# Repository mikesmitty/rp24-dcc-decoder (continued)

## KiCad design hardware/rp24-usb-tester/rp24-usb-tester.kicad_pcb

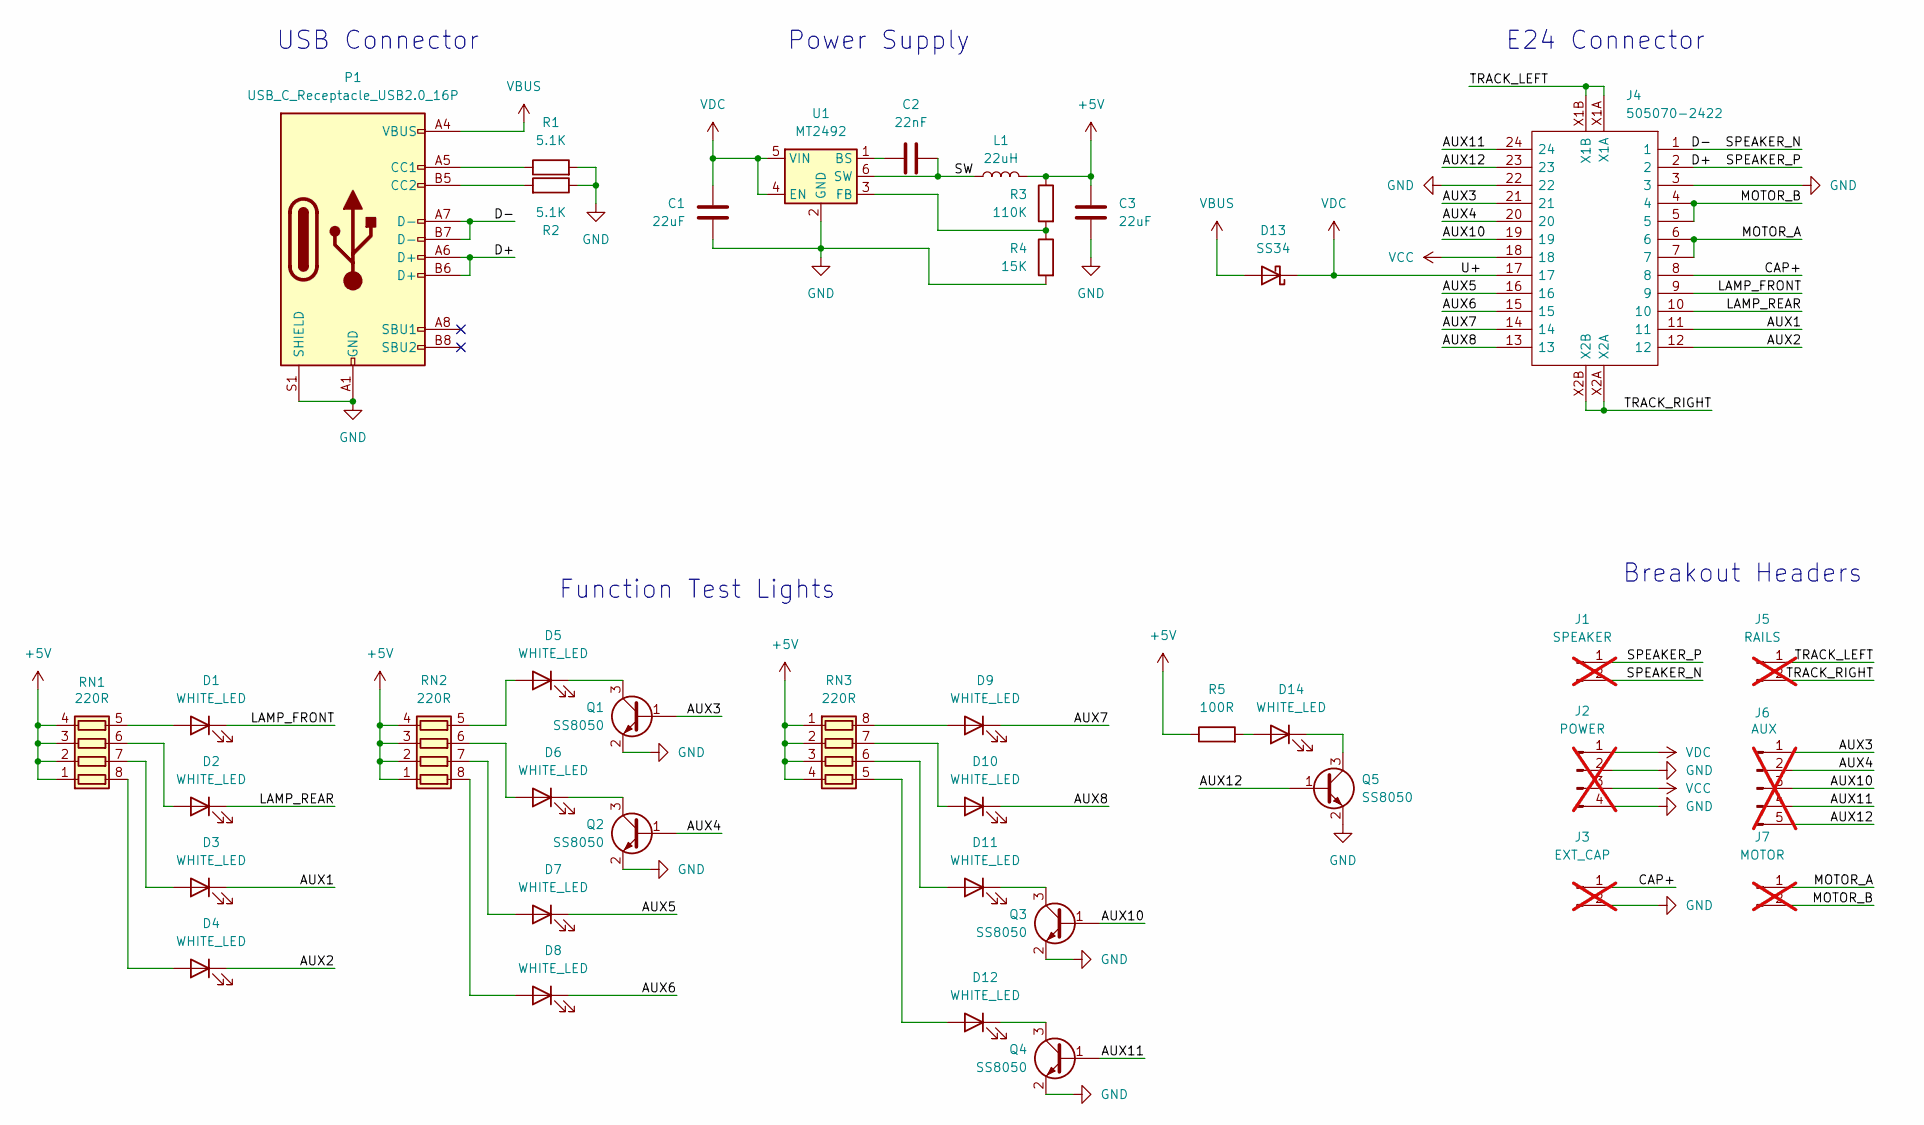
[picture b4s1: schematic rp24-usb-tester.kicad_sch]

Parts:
C1, C3: 22uF; C_0805_2012Metric; LCSC C45783
C2: 22nF; C_0402_1005Metric; LCSC C1532
D1, D2, D3, D4, D5, D6, D7, D8, D9, D10, D11, D12, D14: WHITE_LED; LED_0603_1608Metric; LCSC C2290
D13: SS34; D_SMA; LCSC C8678
J1: SPEAKER; PinHeader_1x02_P2.54mm_Vertical; not fitted
J2: POWER; PinHeader_1x04_P2.54mm_Vertical; not fitted
J3: EXT_CAP; PinHeader_1x02_P2.54mm_Vertical; not fitted
J4: 505070-2422; CONN-SMD_24P-P0.35_5050702422; Manufacturer_Part_Number 505070-2422; LCSC C724143
J5: RAILS; PinHeader_1x02_P2.54mm_Vertical; not fitted
J6: AUX; PinHeader_1x05_P2.54mm_Vertical; not fitted
J7: MOTOR; PinHeader_1x02_P2.54mm_Vertical; not fitted
L1: 22uH; IND-SMD_L4.6-W4.2_SMMS0420; LCSC C2894720
P1: USB_C_Receptacle_USB2.0_16P; USB_C_Receptacle_GCT_USB4105-xx-A_16P_TopMnt_Horizontal; LCSC C2765186
Q1, Q2, Q3, Q4, Q5: SS8050; SOT-23; LCSC C2150
R1, R2: 5.1K; R_0402_1005Metric; LCSC C25905
R3: 110K; R_0603_1608Metric; LCSC C25805
R4: 15K; R_0603_1608Metric; LCSC C22809
R5: 100R; R_0402_1005Metric; LCSC C25076
RN1, RN2, RN3: 220R; R_Array_Concave_4x0402; LCSC C326868
U1: MT2492; SOT-23-6; LCSC C89358

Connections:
+5V: C3.1, L1.2, R3.1, R5.1, RN1.1 (R1.1), RN1.2 (R2.1), RN1.3 (R3.1), RN1.4 (R4.1), RN2.1 (R1.1), RN2.2 (R2.1), RN2.3 (R3.1), RN2.4 (R4.1), RN3.1 (R1.1), RN3.2 (R2.1), RN3.3 (R3.1), RN3.4 (R4.1)
/AUX1: D3.1 (K), J4.11
/AUX2: D4.1 (K), J4.12
/AUX3: J4.21, J6.1, Q1.1 (B)
/AUX4: J4.20, J6.2, Q2.1 (B)
/AUX5: D7.1 (K), J4.16
/AUX6: D8.1 (K), J4.15
/AUX7: D9.1 (K), J4.14
/AUX8: D10.1 (K), J4.13
/AUX10: J4.19, J6.3, Q3.1 (B)
/AUX11: J4.24, J6.4, Q4.1 (B)
/AUX12: J4.23, J6.5, Q5.1 (B)
/CAP+: J3.1, J4.8
/D+: J1.1, J4.2, P1.A6 (D+), P1.B6 (D+)
/D-: J1.2, J4.1, P1.A7 (D-), P1.B7 (D-)
/LAMP_FRONT: D1.1 (K), J4.9
/LAMP_REAR: D2.1 (K), J4.10
/MOTOR_A: J4.6, J4.7, J7.1
/MOTOR_B: J4.4, J4.5, J7.2
/SW: C2.2, L1.1, U1.6 (SW)
/TRACK_LEFT: J4.X1A, J4.X1B, J5.1
/TRACK_RIGHT: J4.X2A, J4.X2B, J5.2
GND: C1.2, C3.2, J2.2, J2.4, J3.2, J4.3, J4.22, P1.A1 (GND), P1.A12 (GND), P1.B1 (GND), P1.B12 (GND), P1.S1 (SHIELD), Q1.2 (E), Q2.2 (E), Q3.2 (E), Q4.2 (E), Q5.2 (E), R1.2, R2.1, R4.2, U1.2 (GND)
unnamed: D1.2 (A), RN1.5 (R4.2)
unnamed: D2.2 (A), RN1.6 (R3.2)
unnamed: D3.2 (A), RN1.7 (R2.2)
unnamed: D4.2 (A), RN1.8 (R1.2)
unnamed: D5.2 (A), RN2.5 (R4.2)
unnamed: D5.1 (K), Q1.3 (C)
unnamed: D6.2 (A), RN2.6 (R3.2)
unnamed: D6.1 (K), Q2.3 (C)
unnamed: D7.2 (A), RN2.7 (R2.2)
unnamed: D8.2 (A), RN2.8 (R1.2)
unnamed: D9.2 (A), RN3.8 (R1.2)
unnamed: D10.2 (A), RN3.7 (R2.2)
unnamed: D11.2 (A), RN3.6 (R3.2)
unnamed: D11.1 (K), Q3.3 (C)
unnamed: D12.2 (A), RN3.5 (R4.2)
unnamed: D12.1 (K), Q4.3 (C)
unnamed: D14.2 (A), R5.2
unnamed: D14.1 (K), Q5.3 (C)
unnamed: P1.A5 (CC1), R1.1
unnamed: P1.B5 (CC2), R2.2
unnamed: C2.1, U1.1 (BS)
unnamed: R3.2, R4.1, U1.3 (FB)
VBUS: D13.2 (A), P1.A4 (VBUS), P1.A9 (VBUS), P1.B4 (VBUS), P1.B9 (VBUS)
VCC: J2.3, J4.18
VDC: C1.1, D13.1 (K), J2.1, J4.17, U1.4 (EN), U1.5 (VIN)

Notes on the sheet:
Function Test Lights
Breakout Headers
E24 Connector
Power Supply
USB Connector

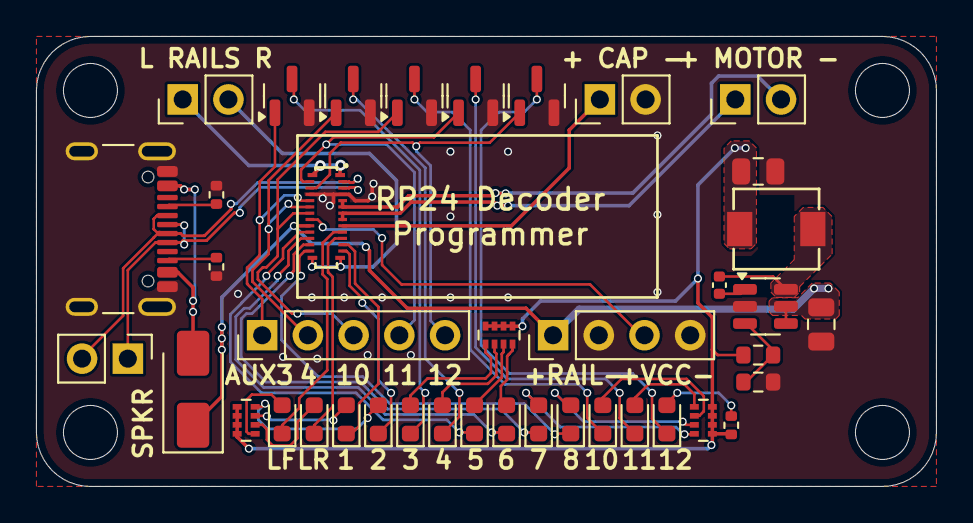
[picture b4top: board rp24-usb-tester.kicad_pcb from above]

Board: 2 copper layers, 50.0 x 25.0 mm, 40 parts (0 on the bottom side), 48 nets.

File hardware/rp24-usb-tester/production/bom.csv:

Comment,Designator,Footprint,LCSC
22uF,"C1,C3",rp24-usb-tester:C_0805_2012Metric,C45783
SS34,D13,rp24-usb-tester:D_SMA,C8678
15K,R4,rp24-usb-tester:R_0603_1608Metric,C22809
WHITE_LED,"D1,D2,D3,D4,D5,D6,D7,D8,D9,D10,D11,D12,D14",rp24-usb-tester:LED_0603_1608Metric,C2290
505070-2422,J4,rp24-usb-tester:CONN-SMD_24P-P0.35_5050702422,C724143
5.1K,"R1,R2",rp24-usb-tester:R_0402_1005Metric,C25905
USB_C_Receptacle_USB2.0_16P,P1,rp24-usb-tester:USB_C_Receptacle_GCT_USB4105-xx-A_16P_TopMnt_Horizontal,C2765186
SS8050,"Q1,Q2,Q3,Q4,Q5",rp24-usb-tester:SOT-23,C2150
220R,"RN1,RN2,RN3",rp24-usb-tester:R_Array_Concave_4x0402,C326868
100R,R5,rp24-usb-tester:R_0402_1005Metric,C25076
22nF,C2,rp24-usb-tester:C_0402_1005Metric,C1532
MT2492,U1,rp24-usb-tester:SOT-23-6,C89358
22uH,L1,rp24-usb-tester:IND-SMD_L4.6-W4.2_SMMS0420,C2894720
110K,R3,rp24-usb-tester:R_0603_1608Metric,C25805

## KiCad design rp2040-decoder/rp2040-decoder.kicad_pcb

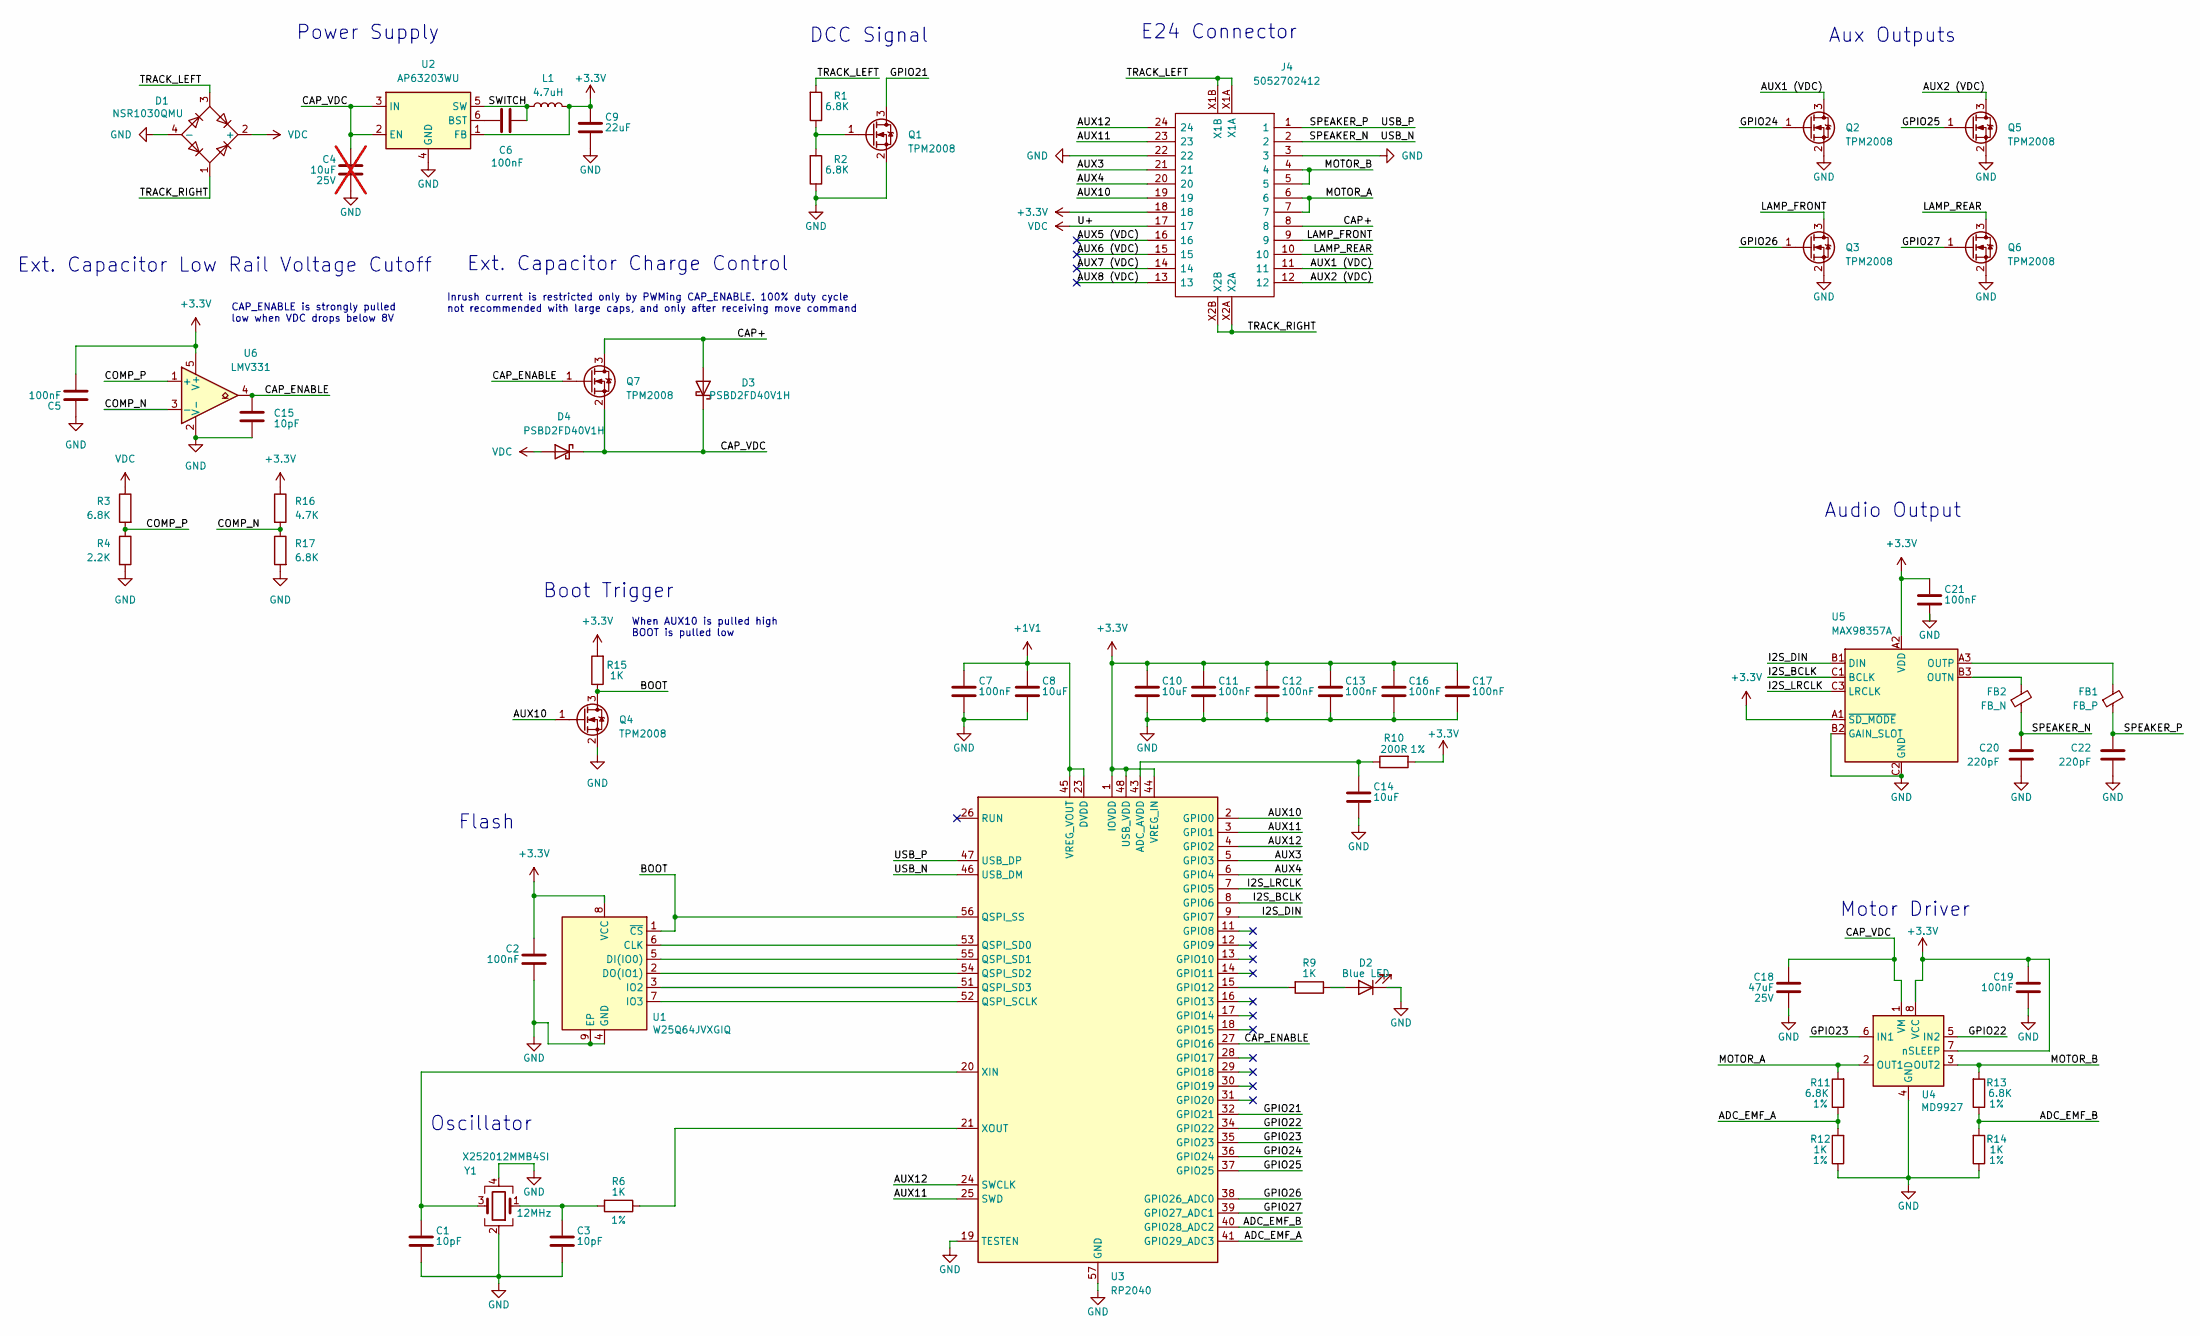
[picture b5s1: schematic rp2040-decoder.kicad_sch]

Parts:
C1, C3, C15: 10pF; C_0201_0603Metric; Voltage 25V; LCSC C384956
C2, C11, C12, C13, C16, C17, C21: 100nF; C_0201_0603Metric; Voltage 6V3; LCSC C49062
C4: 10uF; C_0603_1608Metric; Voltage 25V; LCSC C96446; not fitted
C5, C6, C19: 100nF; C_0201_0603Metric; LCSC C49062
C7: 100nF; C_0201_0603Metric; Voltage 2V5; LCSC C49062
C8: 10uF; C_0402_1005Metric; Voltage 2V5; LCSC C15525
C9: 22uF; C_0603_1608Metric; LCSC C86295
C10, C14: 10uF; C_0402_1005Metric; Voltage 6V3; LCSC C15525
C18: 47uF; C_1206_3216Metric; Voltage 25V; LCSC C403725
C20, C22: 220pF; C_0201_0603Metric; LCSC C62548
D1: NSR1030QMU; LCSC C889734
D2: Blue LED; LED_0402_1005Metric; LCSC C130724
D3, D4: PSBD2FD40V1H; D_SOD-882; LCSC C492733
FB1: FB_P; L_0402_1005Metric; LCSC C160973
FB2: FB_N; L_0402_1005Metric; LCSC C160973
J4: 5052702412; 5050662422; Manufacturer_Part_Number 505270-2412; LCSC C724151
L1: 4.7uH; L_1008_2520Metric; LCSC C5832360
Q1, Q2, Q3, Q4, Q5, Q6, Q7: TPM2008; Diodes_DFN1006-3; LCSC C2827633
R1, R2: 6.8K; R_0201_0603Metric; Tolerance 10%; LCSC C423451
R3, R17: 6.8K; R_0201_0603Metric; LCSC C423451
R4: 2.2K; R_0201_0603Metric; LCSC C473534
R6, R12, R14: 1K; R_0201_0603Metric; Tolerance 1%; LCSC C270365
R9, R15: 1K; R_0201_0603Metric; Tolerance 10%; LCSC C270365
R10: 200R; R_0201_0603Metric; Tolerance 1%; LCSC C270359
R11, R13: 6.8K; R_0201_0603Metric; Tolerance 1%; LCSC C423451
R16: 4.7K; R_0201_0603Metric; LCSC C270346
U1: W25Q64JVXGIQ; WSON-8-1EP_4x4mm_P0.8mm_EP2.2x3mm; LCSC C2940195
U2: AP63203WU; TSOT-23-6; LCSC C780769
U3: RP2040; QFN-56-1EP_7x7mm_P0.4mm_EP3.2x3.2mm; LCSC C2040
U4: MD9927; LM293QT; LCSC C2684662
U5: MAX98357A; Maxim_WLP-9_1.595x1.415_Layout3x3_P0.4mm_Ball0.27mm_Pad0.25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; LCSC C2682619
U6: LMV331; SOT-353_SC-70-5; LCSC C7976
Y1: X252012MMB4SI; Crystal_SMD_2520-4Pin_2.5x2.0mm; LCSC C2896601

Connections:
+1V1: C7.1, C8.1, U3.23 (DVDD), U3.45 (VREG_VOUT), U3.50 (DVDD)
+3.3V: C2.1, C5.2, C9.1, C10.1, C11.1, C12.1, C13.1, C16.1, C17.1, C19.1, C21.1, J4.18, L1.2, R10.1, R15.2, R16.1, U1.8 (VCC), U2.1 (FB), U3.1 (IOVDD), U3.10 (IOVDD), U3.22 (IOVDD), U3.33 (IOVDD), U3.42 (IOVDD), U3.44 (VREG_IN), U3.48 (USB_VDD), U3.49 (IOVDD), U4.7 (nSLEEP), U4.8 (VCC), U5.A1 (~SD_MODE), U5.A2 (VDD), U6.5 (V+)
/ADC_EMF_A: R11.1, R12.2, U3.41 (GPIO29_ADC3)
/ADC_EMF_B: R13.1, R14.2, U3.40 (GPIO28_ADC2)
/AUX1 (VDC): J4.11, Q2.3 (D)
/AUX2 (VDC): J4.12, Q5.3 (D)
/AUX3: J4.21, U3.5 (GPIO3)
/AUX4: J4.20, U3.6 (GPIO4)
/AUX5 (VDC): J4.16
/AUX6 (VDC): J4.15
/AUX7 (VDC): J4.14
/AUX8 (VDC): J4.13
/AUX10: J4.19, Q4.1 (G), U3.2 (GPIO0)
/AUX11: J4.23, U3.3 (GPIO1), U3.25 (SWD)
/AUX12: J4.24, U3.4 (GPIO2), U3.24 (SWCLK)
/BOOT: Q4.3 (D), R15.1, U1.1 (~CS), U3.56 (QSPI_SS)
/CAP+: D3.2 (A), J4.8, Q7.3 (D)
/CAP_ENABLE: C15.1, Q7.1 (G), U3.27 (GPIO16), U6.4
/CAP_VDC: C4.1, C18.1, D3.1 (K), D4.1 (K), Q7.2 (S), U2.2 (EN), U2.3 (IN), U4.1 (VM)
/COMP_N: R16.2, R17.1, U6.3 (-)
/COMP_P: R3.2, R4.1, U6.1 (+)
/GPIO21: Q1.3 (D), U3.32 (GPIO21)
/GPIO22: U3.34 (GPIO22), U4.5 (IN2)
/GPIO23: U3.35 (GPIO23), U4.6 (IN1)
/GPIO24: Q2.1 (G), U3.36 (GPIO24)
/GPIO25: Q5.1 (G), U3.37 (GPIO25)
/GPIO26: Q3.1 (G), U3.38 (GPIO26_ADC0)
/GPIO27: Q6.1 (G), U3.39 (GPIO27_ADC1)
/I2S_BCLK: U3.8 (GPIO6), U5.C1 (BCLK)
/I2S_DIN: U3.9 (GPIO7), U5.B1 (DIN)
/I2S_LRCLK: U3.7 (GPIO5), U5.C3 (LRCLK)
/LAMP_FRONT: J4.9, Q3.3 (D)
/LAMP_REAR: J4.10, Q6.3 (D)
/MOTOR_A: J4.6, J4.7, R11.2, U4.2 (OUT1)
/MOTOR_B: J4.4, J4.5, R13.2, U4.3 (OUT2)
/SPEAKER_N: C20.1, FB2.1, J4.2, U3.46 (USB_DM)
/SPEAKER_P: C22.1, FB1.1, J4.1, U3.47 (USB_DP)
/SWITCH: C6.2, L1.1, U2.5 (SW)
/TRACK_LEFT: D1.3, J4.X1A, J4.X1B, R1.2
/TRACK_RIGHT: D1.1, J4.X2A, J4.X2B
GND: C1.2, C2.2, C3.2, C4.2, C5.1, C7.2, C8.2, C9.2, C10.2, C11.2, C12.2, C13.2, C14.2, C15.2, C16.2, C17.2, C18.2, C19.2, C20.2, C21.2, C22.2, D1.4 (-), D2.1 (K), J4.3, J4.22, Q1.2 (S), Q2.2 (S), Q3.2 (S), Q4.2 (S), Q5.2 (S), Q6.2 (S), R2.1, R4.2, R12.1, R14.1, R17.2, U1.4 (GND), U1.9 (EP), U2.4 (GND), U3.19 (TESTEN), U3.57 (GND), U4.4 (GND), U4.9 (GND), U5.B2 (GAIN_SLOT), U5.C2 (GND), U6.2 (V-), Y1.2, Y1.4
unnamed: C3.1, R6.2, Y1.1
unnamed: D2.2 (A), R9.1
unnamed: Q1.1 (G), R1.1, R2.2
unnamed: U1.6 (CLK), U3.53 (QSPI_SD0)
unnamed: U1.5 (DI(IO0)), U3.55 (QSPI_SD1)
unnamed: U1.2 (DO(IO1)), U3.54 (QSPI_SD2)
unnamed: U1.3 (IO2), U3.51 (QSPI_SD3)
unnamed: U1.7 (IO3), U3.52 (QSPI_SCLK)
unnamed: C6.1, U2.6 (BST)
unnamed: C14.1, R10.2, U3.43 (ADC_AVDD)
unnamed: R9.2, U3.15 (GPIO12)
unnamed: C1.1, U3.20 (XIN), Y1.3
unnamed: R6.1, U3.21 (XOUT)
unnamed: FB2.2, U5.B3 (OUTN)
unnamed: FB1.2, U5.A3 (OUTP)
VDC: D1.2 (+), D4.2 (A), J4.17, R3.1

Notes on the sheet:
Inrush current is restricted only by PWMing CAP_ENABLE. 100% duty cycle not recommended with large caps, and only after receiving move command
Boot Trigger
CAP_ENABLE is strongly pulled low when VDC drops below 8V
Aux Outputs
Motor Driver
Oscillator
Power Supply
Flash
Ext. Capacitor Low Rail Voltage Cutoff
Ext. Capacitor Charge Control
Audio Output
E24 Connector
When AUX10 is pulled high BOOT is pulled low
DCC Signal

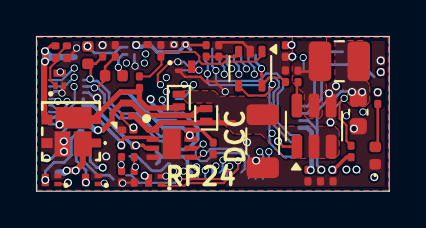
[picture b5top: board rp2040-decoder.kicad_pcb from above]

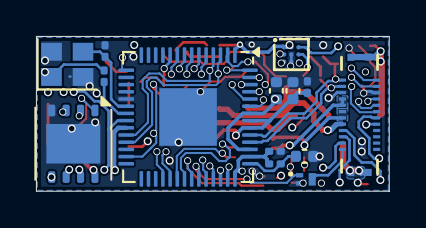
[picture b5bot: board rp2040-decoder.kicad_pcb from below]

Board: 4 copper layers, 19.6 x 8.6 mm, 57 parts (14 on the bottom side), 53 nets.

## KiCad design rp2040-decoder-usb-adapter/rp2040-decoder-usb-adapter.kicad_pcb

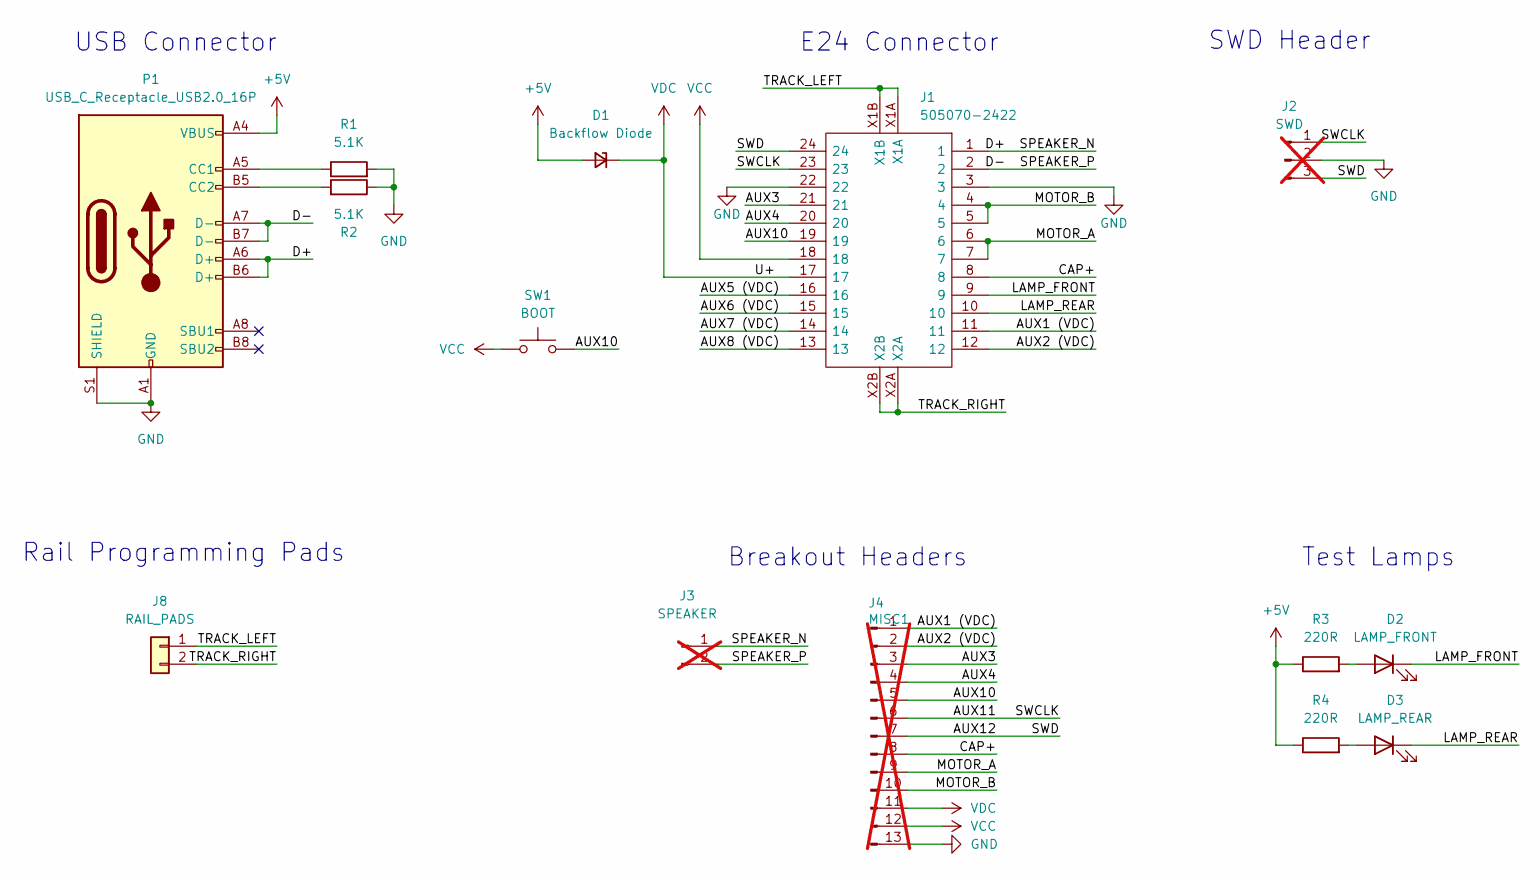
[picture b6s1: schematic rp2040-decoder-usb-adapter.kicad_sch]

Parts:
D1: Backflow Diode; D_SOD-323_HandSoldering; LCSC C2903905
D2: LAMP_FRONT; LED_0603_1608Metric_Pad1.05x0.95mm_HandSolder; LCSC C2290
D3: LAMP_REAR; LED_0603_1608Metric_Pad1.05x0.95mm_HandSolder; LCSC C2290
J1: 505070-2422; 5050702422; Manufacturer_Part_Number 505070-2422; LCSC C724143
J2: SWD; PinHeader_1x03_P2.54mm_Vertical; not fitted
J3: SPEAKER; PinHeader_1x02_P2.54mm_Vertical; not fitted
J4: MISC1; PinHeader_1x13_P2.54mm_Vertical; not fitted
J8: RAIL_PADS; N_Gauge_Rail
P1: USB_C_Receptacle_USB2.0_16P; USB_C_Receptacle_GCT_USB4105-xx-A_16P_TopMnt_Horizontal; LCSC C2765186
R1, R2: 5.1K; R_0805_2012Metric_Pad1.20x1.40mm_HandSolder; LCSC C27834
R3, R4: 220R; R_0805_2012Metric_Pad1.20x1.40mm_HandSolder; LCSC C22962
SW1: BOOT; SW_Push_1P1T_NO_Vertical_Wuerth_434133025816; LCSC C5504987

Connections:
+5V: D1.2 (A), P1.A4 (VBUS), P1.A9 (VBUS), P1.B4 (VBUS), P1.B9 (VBUS), R3.1, R4.1
/AUX1 (VDC): J1.11, J4.1
/AUX2 (VDC): J1.12, J4.2
/AUX3: J1.21, J4.3
/AUX4: J1.20, J4.4
/AUX5 (VDC): J1.16
/AUX6 (VDC): J1.15
/AUX7 (VDC): J1.14
/AUX8 (VDC): J1.13
/AUX10: J1.19, J4.5, SW1.2
/AUX11: J1.23, J2.1, J4.6
/AUX12: J1.24, J2.3, J4.7
/CAP+: J1.8, J4.8
/D+: J1.1, J3.1, P1.A6 (D+), P1.B6 (D+)
/D-: J1.2, J3.2, P1.A7 (D-), P1.B7 (D-)
/LAMP_FRONT: D2.1 (K), J1.9
/LAMP_REAR: D3.1 (K), J1.10
/MOTOR_A: J1.6, J1.7, J4.9
/MOTOR_B: J1.4, J1.5, J4.10
/TRACK_LEFT: J1.X1A, J1.X1B, J8.1
/TRACK_RIGHT: J1.X2A, J1.X2B, J8.2
GND: J1.3, J1.22, J2.2, J4.13, P1.A1 (GND), P1.A12 (GND), P1.B1 (GND), P1.B12 (GND), P1.S1 (SHIELD), R1.2, R2.1
unnamed: D2.2 (A), R3.2
unnamed: D3.2 (A), R4.2
unnamed: P1.A5 (CC1), R1.1
unnamed: P1.B5 (CC2), R2.2
VCC: J1.18, J4.12, SW1.1
VDC: D1.1 (K), J1.17, J4.11

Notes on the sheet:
Rail Programming Pads
E24 Connector
SWD Header
USB Connector
Test Lamps
Breakout Headers

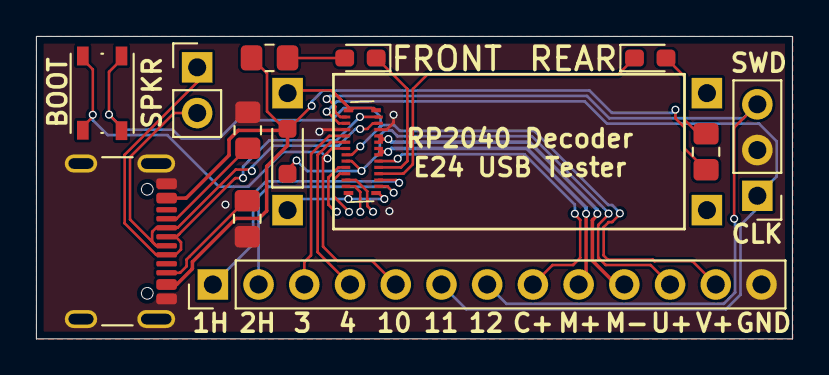
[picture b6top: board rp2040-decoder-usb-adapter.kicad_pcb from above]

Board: 2 copper layers, 42.0 x 16.8 mm, 14 parts (1 on the bottom side), 24 nets.

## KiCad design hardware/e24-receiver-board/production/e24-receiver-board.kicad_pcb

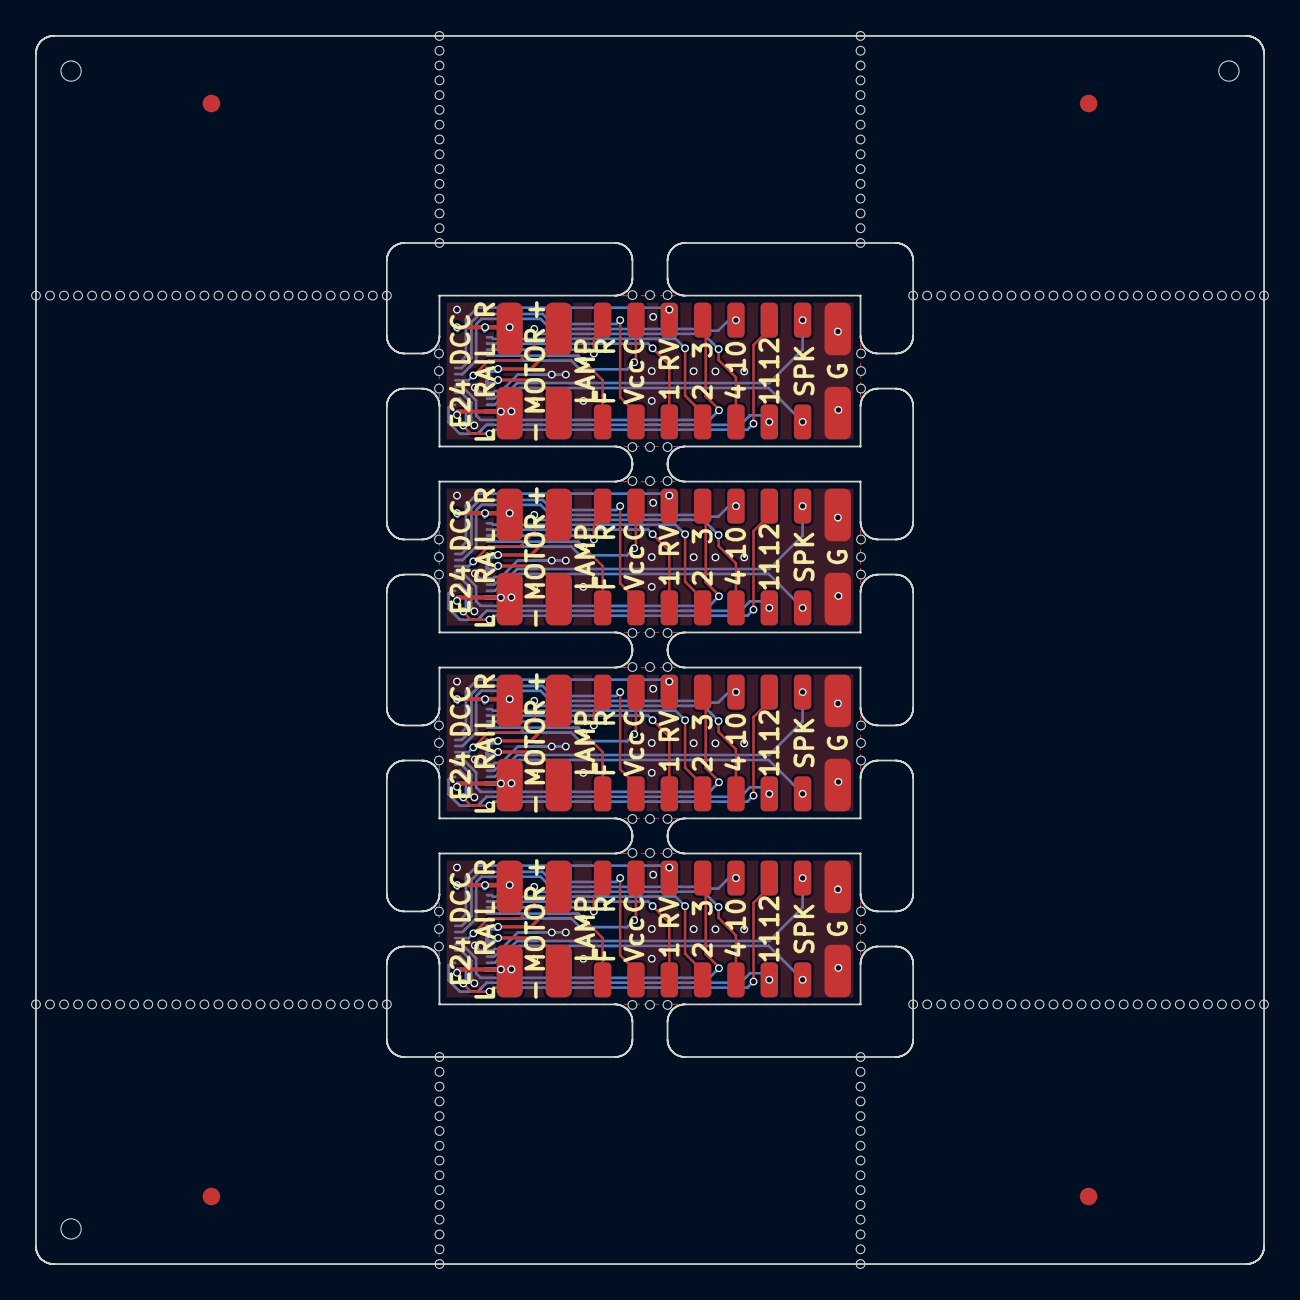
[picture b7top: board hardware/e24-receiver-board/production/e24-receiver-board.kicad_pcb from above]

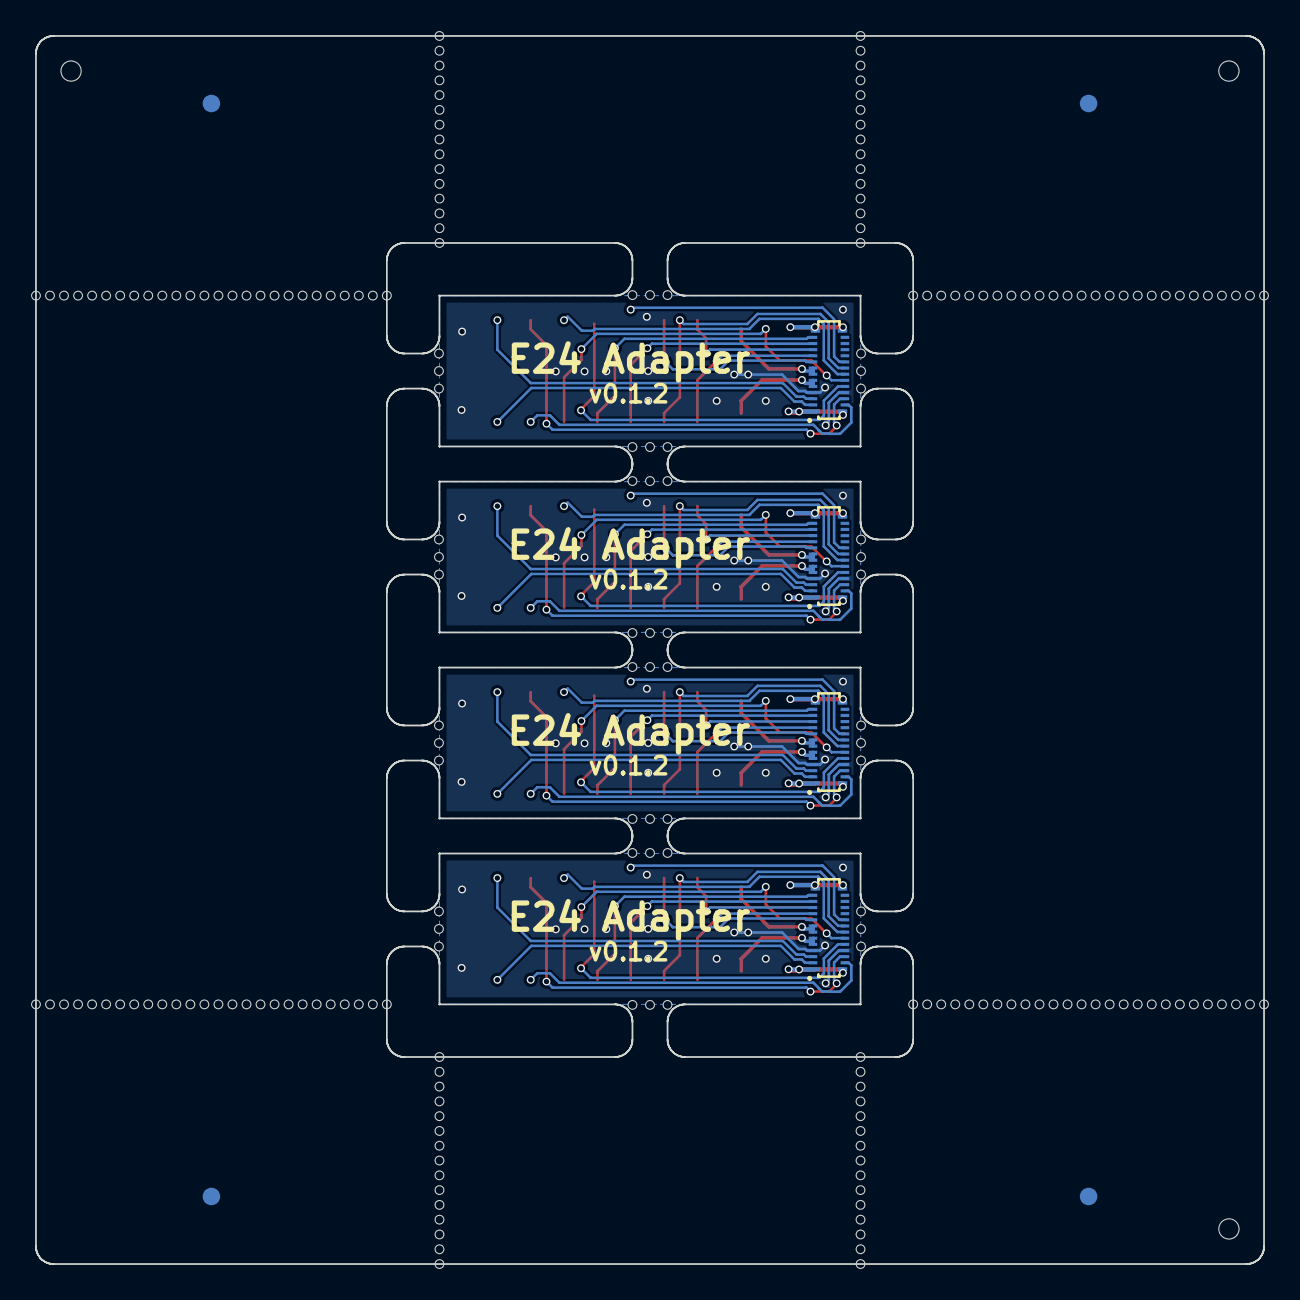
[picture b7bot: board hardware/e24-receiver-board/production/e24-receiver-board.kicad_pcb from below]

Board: 2 copper layers, 70.0 x 70.0 mm, 307 parts (8 on the bottom side), 76 nets.

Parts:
J1, J1#2, J1#3, J1#4: 505070-2422; CONN-SMD_24P-P0.35_5050702422
J2, J2#2, J2#3, J2#4: TRACK_LEFT; SolderWirePad_1x01_SMD_1.5x3mm
J3, J3#2, J3#3, J3#4: MOTOR-; SolderWirePad_1x01_SMD_1.5x3mm
J4, J4#2, J4#3, J4#4: LAMP_FRONT; SolderWirePad_1x01_SMD_1x2mm
J5, J5#2, J5#3, J5#4: VCC; SolderWirePad_1x01_SMD_1x2mm
J6, J6#2, J6#3, J6#4: AUX1; SolderWirePad_1x01_SMD_1x2mm
J7, J7#2, J7#3, J7#4: AUX2; SolderWirePad_1x01_SMD_1x2mm
J8, J8#2, J8#3, J8#4: AUX4; SolderWirePad_1x01_SMD_1x2mm
J9, J9#2, J9#3, J9#4: AUX11; SolderWirePad_1x01_SMD_1x2mm
J10, J10#2, J10#3, J10#4: SPEAKER-; SolderWirePad_1x01_SMD_1x2mm
J11, J11#2, J11#3, J11#4: GND1; SolderWirePad_1x01_SMD_1.5x3mm
J12, J12#2, J12#3, J12#4: TRACK_RIGHT; SolderWirePad_1x01_SMD_1.5x3mm
J13, J13#2, J13#3, J13#4: MOTOR+; SolderWirePad_1x01_SMD_1.5x3mm
J14, J14#2, J14#3, J14#4: LAMP_REAR; SolderWirePad_1x01_SMD_1x2mm
J15, J15#2, J15#3, J15#4: CAP+; SolderWirePad_1x01_SMD_1x2mm
J16, J16#2, J16#3, J16#4: U+; SolderWirePad_1x01_SMD_1x2mm
J17, J17#2, J17#3, J17#4: AUX3; SolderWirePad_1x01_SMD_1x2mm
J18, J18#2, J18#3, J18#4: AUX10; SolderWirePad_1x01_SMD_1x2mm
J19, J19#2, J19#3, J19#4: AUX12; SolderWirePad_1x01_SMD_1x2mm
J20, J20#2, J20#3, J20#4: SPEAKER+; SolderWirePad_1x01_SMD_1x2mm
J21, J21#2, J21#3, J21#4: GND2; SolderWirePad_1x01_SMD_1.5x3mm
KiKit_FID_B_1, KiKit_FID_B_2, KiKit_FID_B_3, KiKit_FID_B_4: Fiducial
KiKit_FID_T_1, KiKit_FID_T_2, KiKit_FID_T_3, KiKit_FID_T_4: Fiducial
KiKit_MB_1_1, KiKit_MB_1_2, KiKit_MB_1_3, KiKit_MB_2_1, KiKit_MB_2_2, KiKit_MB_2_3, KiKit_MB_3_1, KiKit_MB_3_2, KiKit_MB_3_3, KiKit_MB_4_1, KiKit_MB_4_2, KiKit_MB_4_3, KiKit_MB_5_1, KiKit_MB_5_2, KiKit_MB_5_3, KiKit_MB_6_1, KiKit_MB_6_2, KiKit_MB_6_3, KiKit_MB_7_1, KiKit_MB_7_2, KiKit_MB_7_3, KiKit_MB_8_1, KiKit_MB_8_2, KiKit_MB_8_3, KiKit_MB_9_1, KiKit_MB_9_2, KiKit_MB_9_3, KiKit_MB_10_1, KiKit_MB_10_2, KiKit_MB_10_3, KiKit_MB_11_1, KiKit_MB_11_2, KiKit_MB_11_3, KiKit_MB_12_1, KiKit_MB_12_2, KiKit_MB_12_3, KiKit_MB_13_1, KiKit_MB_13_2, KiKit_MB_13_3, KiKit_MB_14_1, KiKit_MB_14_2, KiKit_MB_14_3, KiKit_MB_15_1, KiKit_MB_15_2, KiKit_MB_15_3, KiKit_MB_16_1, KiKit_MB_16_2, KiKit_MB_16_3, KiKit_MB_17_1, KiKit_MB_17_2, KiKit_MB_17_3, KiKit_MB_17_4, KiKit_MB_17_5, KiKit_MB_17_6, KiKit_MB_17_7, KiKit_MB_17_8, KiKit_MB_17_9, KiKit_MB_17_10, KiKit_MB_17_11, KiKit_MB_17_12, KiKit_MB_17_13, KiKit_MB_17_14, KiKit_MB_17_15, KiKit_MB_18_1, KiKit_MB_18_2, KiKit_MB_18_3, KiKit_MB_18_4, KiKit_MB_18_5, KiKit_MB_18_6, KiKit_MB_18_7, KiKit_MB_18_8, KiKit_MB_18_9, KiKit_MB_18_10, KiKit_MB_18_11, KiKit_MB_18_12, KiKit_MB_18_13, KiKit_MB_18_14, KiKit_MB_18_15, KiKit_MB_19_1, KiKit_MB_19_2, KiKit_MB_19_3, KiKit_MB_19_4, KiKit_MB_19_5, KiKit_MB_19_6, KiKit_MB_19_7, KiKit_MB_19_8, KiKit_MB_19_9, KiKit_MB_19_10, KiKit_MB_19_11, KiKit_MB_19_12, KiKit_MB_19_13, KiKit_MB_19_14, KiKit_MB_19_15, KiKit_MB_20_1, KiKit_MB_20_2, KiKit_MB_20_3, KiKit_MB_20_4, KiKit_MB_20_5, KiKit_MB_20_6, KiKit_MB_20_7, KiKit_MB_20_8, KiKit_MB_20_9, KiKit_MB_20_10, KiKit_MB_20_11, KiKit_MB_20_12, KiKit_MB_20_13, KiKit_MB_20_14, KiKit_MB_20_15, KiKit_MB_21_1, KiKit_MB_21_2, KiKit_MB_21_3, KiKit_MB_21_4, KiKit_MB_21_5, KiKit_MB_21_6, KiKit_MB_21_7, KiKit_MB_21_8, KiKit_MB_21_9, KiKit_MB_21_10, KiKit_MB_21_11, KiKit_MB_21_12, KiKit_MB_21_13, KiKit_MB_21_14, KiKit_MB_21_15, KiKit_MB_21_16, KiKit_MB_21_17, KiKit_MB_21_18, KiKit_MB_21_19, KiKit_MB_21_20, KiKit_MB_21_21, KiKit_MB_21_22, KiKit_MB_21_23, KiKit_MB_21_24, KiKit_MB_21_25, KiKit_MB_21_26, KiKit_MB_22_1, KiKit_MB_22_2, KiKit_MB_22_3, KiKit_MB_22_4, KiKit_MB_22_5, KiKit_MB_22_6, KiKit_MB_22_7, KiKit_MB_22_8, KiKit_MB_22_9, KiKit_MB_22_10, KiKit_MB_22_11, KiKit_MB_22_12, KiKit_MB_22_13, KiKit_MB_22_14, KiKit_MB_22_15, KiKit_MB_22_16, KiKit_MB_22_17, KiKit_MB_22_18, KiKit_MB_22_19, KiKit_MB_22_20, KiKit_MB_22_21, KiKit_MB_22_22, KiKit_MB_22_23, KiKit_MB_22_24, KiKit_MB_22_25, KiKit_MB_22_26, KiKit_MB_23_1, KiKit_MB_23_2, KiKit_MB_23_3, KiKit_MB_23_4, KiKit_MB_23_5, KiKit_MB_23_6, KiKit_MB_23_7, KiKit_MB_23_8, KiKit_MB_23_9, KiKit_MB_23_10, KiKit_MB_23_11, KiKit_MB_23_12, KiKit_MB_23_13, KiKit_MB_23_14, KiKit_MB_23_15, KiKit_MB_23_16, KiKit_MB_23_17, KiKit_MB_23_18, KiKit_MB_23_19, KiKit_MB_23_20, KiKit_MB_23_21, KiKit_MB_23_22, KiKit_MB_23_23, KiKit_MB_23_24, KiKit_MB_23_25, KiKit_MB_23_26, KiKit_MB_24_1, KiKit_MB_24_2, KiKit_MB_24_3, KiKit_MB_24_4, KiKit_MB_24_5, KiKit_MB_24_6, KiKit_MB_24_7, KiKit_MB_24_8, KiKit_MB_24_9, KiKit_MB_24_10, KiKit_MB_24_11, KiKit_MB_24_12, KiKit_MB_24_13, KiKit_MB_24_14, KiKit_MB_24_15, KiKit_MB_24_16, KiKit_MB_24_17, KiKit_MB_24_18, KiKit_MB_24_19, KiKit_MB_24_20, KiKit_MB_24_21, KiKit_MB_24_22, KiKit_MB_24_23, KiKit_MB_24_24, KiKit_MB_24_25, KiKit_MB_24_26: NPTH
KiKit_TO_1, KiKit_TO_2, KiKit_TO_3: NPTH

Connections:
Board_0-/AUX1 (VDC): J1#4.11, J6.1
Board_0-/AUX2 (VDC): J1#4.12, J7#3.1
Board_0-/AUX3: J1#4.21, J17.1
Board_0-/AUX4: J1#4.20, J8#3.1
Board_0-/AUX10: J1#4.19, J18#3.1
Board_0-/AUX11: J1#4.24, J9#4.1
Board_0-/AUX12: J1#4.23, J19#3.1
Board_0-/CAP+: J1#4.8, J15#2.1
Board_0-/LAMP_FRONT: J1#4.9, J4#3.1
Board_0-/LAMP_REAR: J1#4.10, J14.1
Board_0-/MOTOR_A: J1#4.6, J1#4.7, J13#3.1
Board_0-/MOTOR_B: J1#4.4, J1#4.5, J3#2.1
Board_0-/SPEAKER_N: J1#4.1, J10#3.1
Board_0-/SPEAKER_P: J1#4.2, J20#3.1
Board_0-/TRACK_LEFT: J1#4.X1A, J1#4.X1B, J2.1
Board_0-/TRACK_RIGHT: J1#4.X2A, J1#4.X2B, J12.1
Board_0-GND: J1#4.3, J1#4.22, J11#4.1, J21#3.1
Board_0-VCC: J1#4.18, J5#4.1
Board_0-VDC: J1#4.17, J16.1
Board_1-/AUX1 (VDC): J1#3.11, J6#3.1
Board_1-/AUX2 (VDC): J1#3.12, J7#4.1
Board_1-/AUX3: J1#3.21, J17#2.1
Board_1-/AUX4: J1#3.20, J8#2.1
Board_1-/AUX10: J1#3.19, J18#2.1
Board_1-/AUX11: J1#3.24, J9#2.1
Board_1-/AUX12: J1#3.23, J19#4.1
Board_1-/CAP+: J1#3.8, J15#4.1
Board_1-/LAMP_FRONT: J1#3.9, J4#4.1
Board_1-/LAMP_REAR: J1#3.10, J14#2.1
Board_1-/MOTOR_A: J1#3.6, J1#3.7, J13.1
Board_1-/MOTOR_B: J1#3.4, J1#3.5, J3#3.1
Board_1-/SPEAKER_N: J1#3.1, J10#4.1
Board_1-/SPEAKER_P: J1#3.2, J20.1
Board_1-/TRACK_LEFT: J1#3.X1A, J1#3.X1B, J2#4.1
Board_1-/TRACK_RIGHT: J1#3.X2A, J1#3.X2B, J12#4.1
Board_1-GND: J1#3.3, J1#3.22, J11.1, J21.1
Board_1-VCC: J1#3.18, J5#3.1
Board_1-VDC: J1#3.17, J16#2.1
Board_2-/AUX1 (VDC): J1.11, J6#4.1
Board_2-/AUX2 (VDC): J1.12, J7#2.1
Board_2-/AUX3: J1.21, J17#4.1
Board_2-/AUX4: J1.20, J8#4.1
Board_2-/AUX10: J1.19, J18#4.1
Board_2-/AUX11: J1.24, J9.1
Board_2-/AUX12: J1.23, J19.1
Board_2-/CAP+: J1.8, J15#3.1
Board_2-/LAMP_FRONT: J1.9, J4#2.1
Board_2-/LAMP_REAR: J1.10, J14#3.1
Board_2-/MOTOR_A: J1.6, J1.7, J13#4.1
Board_2-/MOTOR_B: J1.4, J1.5, J3#4.1
Board_2-/SPEAKER_N: J1.1, J10#2.1
Board_2-/SPEAKER_P: J1.2, J20#4.1
Board_2-/TRACK_LEFT: J1.X1A, J1.X1B, J2#3.1
Board_2-/TRACK_RIGHT: J1.X2A, J1.X2B, J12#3.1
Board_2-GND: J1.3, J1.22, J11#2.1, J21#4.1
Board_2-VCC: J1.18, J5.1
Board_2-VDC: J1.17, J16#3.1
Board_3-/AUX1 (VDC): J1#2.11, J6#2.1
Board_3-/AUX2 (VDC): J1#2.12, J7.1
Board_3-/AUX3: J1#2.21, J17#3.1
Board_3-/AUX4: J1#2.20, J8.1
Board_3-/AUX10: J1#2.19, J18.1
Board_3-/AUX11: J1#2.24, J9#3.1
Board_3-/AUX12: J1#2.23, J19#2.1
Board_3-/CAP+: J1#2.8, J15.1
Board_3-/LAMP_FRONT: J1#2.9, J4.1
Board_3-/LAMP_REAR: J1#2.10, J14#4.1
Board_3-/MOTOR_A: J1#2.6, J1#2.7, J13#2.1
Board_3-/MOTOR_B: J1#2.4, J1#2.5, J3.1
Board_3-/SPEAKER_N: J1#2.1, J10.1
Board_3-/SPEAKER_P: J1#2.2, J20#2.1
Board_3-/TRACK_LEFT: J1#2.X1A, J1#2.X1B, J2#2.1
Board_3-/TRACK_RIGHT: J1#2.X2A, J1#2.X2B, J12#2.1
Board_3-GND: J1#2.3, J1#2.22, J11#3.1, J21#2.1
Board_3-VCC: J1#2.18, J5#2.1
Board_3-VDC: J1#2.17, J16#4.1
